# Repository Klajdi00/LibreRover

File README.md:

# LibreRover

LibreRover is a open-source, open-hardware educational robot designed for Arduino and robotics workshops.

## Hardware

The hardware parts mostly can be 3D printed. It is designed to fit affordable breakout boards. It is modular and expandable: If you want an encoder, use it. If not, no problem. More sensors? Just print the parts and stick it to the robot.
By using breakout boards for all sensors, the wiring is very flexible, at the cost of lots of wires thorugh the air. For a more permanent setup, consider hot glue and good cable management.

## Software

The Arduino framework is used. Feel free to choose an Arduino Nano (simple), an ESP32 (has WiFi) or another microcontroller. Several classes for an easy start are provided and can be used as needed:
- `Motor`: This makes a simple motor more accessible by taking care of the direction pins and PWM speed control. It is intended to be used with an L298N motor driver.
- `EncoderMotor`: A motor and an encoder together form an EncoderMotor. This class handles both, so the user can easily set the speed and make a wheel move a certain amount.

If you use the Arduino IDE, make sure to add the files in `software/lib/LibreRover` to your project. As an Alternative, consider using PlatformIO.

## Bill of Materials

| Component | Quantity | Estimated Cost | Notes |
|-----------|----------|----------------|-------|
| Arduino Nano | 1 | 3.40 € | Or compatible clone |
| DC Motors with Encoders | 2 | 2.80 € | TT motor; recommended to buy a set with wheels |
| Motor Driver (HW-201 or L298N) | 1 | 2.50 € | Dual H-bridge driver |
| 9V Battery | 1 | 3.50 € | Power supply |
| Jumper Wires | Several | 3.80 € | For connections |
| Light gate LM393 (for simple encoder) | 2 | 3.20 € | optional |
| HW-201 IR reflection sensor | 2 | 1.30 € | optional |
| VL53L0X ToF distance sensor | 3 | 4.00 € | optional |
| Others | - | 1.00 € | 9 V Battery cable, swith for turning on/off |

**Estimated Total Cost**: ~17 to 27 € (depending on your setup; excluding 3D printer)

## Hardware assembly

The mechanical parts are in `hardware/mechanical`. The full assembly is shown in `hardware/mechanical/Rover.f3z`.

1. Print the parts that you need:
	- Body
	- Mounting parts for your set of sensors
2. If you print 3D print the wheels (not recommended): Use rubber foam or similar so that they have some grip on the ground.
3. Assemble the motors
	- Screws work best.
	- As an alternative, use the clams `Clamp_Motor_Nose` and `Clamp_Motor_Body` together with `Pin_Motor`.
4. Assemble the glider by sticking it to the body frame. It will be the third contact point with the ground.
5. Assemble the sensors. The sensor mounts are fixed to the body frame with `Simple_pin` and friction. The distance sensors can be fixed to their mounts either by another pin (`Pin_VL53L0X`) or a clamp (`Clamp_VL53L0X`).
6. The 9V battery can be hold in place by `9V_Block_Mounting` on the bottom side of the frame.
7. Wire the electronics.

## Software setup

### Motor

When using the provided class for a simple motor, make sure to setup the correct pins and values.

The `Motor` needs:
- The pins connected to IN1 and IN 2 from the motor driver board (so set the direction).
- The pin connected to EN from the motor driver board. Make sure that PWM is supported on this pin.
- The minimum PWM value at which the motor starts moving. This is used to scale the speed.
- The maximum PWM value. This limits the effective voltage for the motor. Use it, when the motor is made for 6 V instead of the 9 V of the battery: `255 / (battery voltage) * (max. motor voltage)`.

The `EncoderMotor` takes
- The `Motor` to control
- The `SimpleEncoder` attatched to it
- The circumference of the wheel
- The amount of encoder pulses per revolution
- The maximum speed in mm/s.

```cpp
// Motor(forward_pin, backward_pin, pwm_pin, min_pwm, max_pwm)
Motor motor_left(9, 10, 11, 50, 255 / 9. * 6.5);

// EncoderMotor(motor, encoder, mm_per_revolution, pulses_per_revolution, max_speed)
EncoderMotor enc_motor_left(motor_left, encoder_left, 251, 40, 350);
```

## Software Usage

### Basic Movement Example

```cpp
#include <EncoderMotor.h>

// Initialize motors and encoders

void loop() {
    // Drive forward 250mm at 150mm/s
    motor_left.drive_distance(250, 150);
    motor_right.drive_distance(250, 150);
    
    // Wait for completion
    while(!motor_left.is_stopped() || !motor_right.is_stopped()) {
        // Update speed control and stop motor if target distance is reached
		motor_left.tick();
        motor_right.tick();
    }
}
```

## Credits

For creating the CAD files, I used these models:
- Arduino Nano: Arduino Nano by Nithish Cadex: https://grabcad.com/library/arduino-nano-36
- L298N board: Motor Driver L298n by Nithish Cadex: https://grabcad.com/library/motor-driver-l298n-2
- Light gate: IR motor speed encoder arduino WYC H2010 by Ahmed Asem: https://print.grabcad.com/library/ir-motor-speed-encoder-arduino-wyc-h2010-1
- HW-201 IR reflection sensor: HW-201 by Kevin McAleer: https://grabcad.com/library/hw-201-1
- VL53L0X ToF distance sensor: VL53L0X by Darhl Thomason: https://grabcad.com/library/vl53l0x-4

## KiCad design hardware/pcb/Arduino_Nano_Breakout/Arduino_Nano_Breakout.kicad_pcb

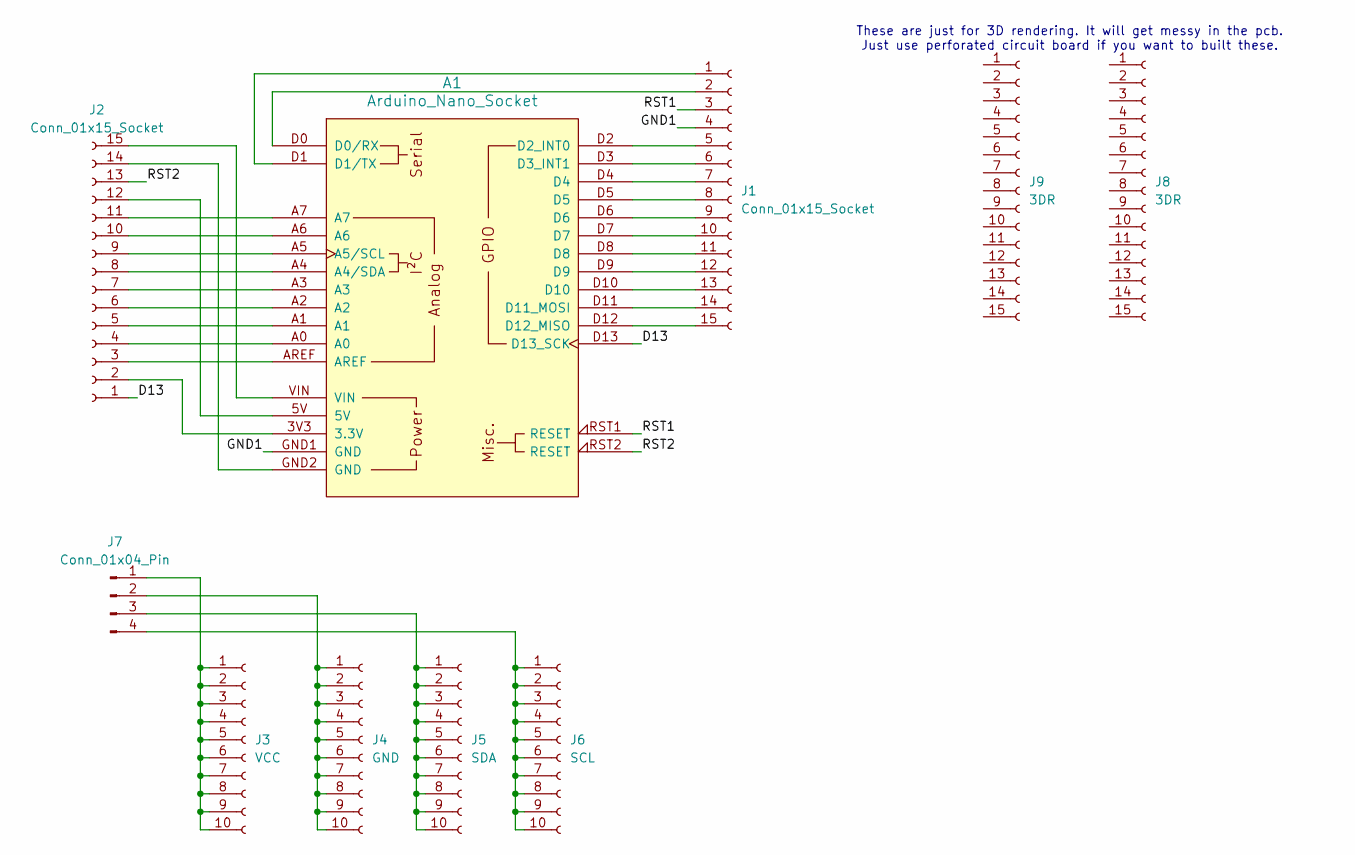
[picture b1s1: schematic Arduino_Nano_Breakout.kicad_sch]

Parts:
A1: Arduino_Nano_Socket
J1, J2: Conn_01x15_Socket; PinSocket_1x15_P2.54mm_Vertical
J3: VCC; PinSocket_1x10_P2.54mm_Vertical
J4: GND; PinSocket_1x10_P2.54mm_Vertical
J5: SDA; PinSocket_1x10_P2.54mm_Vertical
J6: SCL; PinSocket_1x10_P2.54mm_Vertical
J7: Conn_01x04_Pin; PinHeader_1x04_P2.54mm_Vertical
J8, J9: 3DR; PinSocket_1x15_P2.54mm_Vertical

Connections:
/D13: A1.D13 (D13_SCK), J2.1
/GND1: A1.GND1 (GND), J1.4
/RST1: A1.RST1 (RESET), J1.3
/RST2: A1.RST2 (RESET), J2.13
unnamed: A1.3V3 (3.3V), J2.2
unnamed: A1.A4 (A4/SDA), J2.8
unnamed: A1.A5 (A5/SCL), J2.9
unnamed: A1.D0 (D0/RX), J1.2
unnamed: A1.D1 (D1/TX), J1.1
unnamed: A1.D2 (D2_INT0), J1.5
unnamed: A1.D3 (D3_INT1), J1.6
unnamed: A1.D11 (D11_MOSI), J1.14
unnamed: A1.D12 (D12_MISO), J1.15
unnamed: A1.D4, J1.7
unnamed: A1.D5, J1.8
unnamed: A1.D6, J1.9
unnamed: A1.D7, J1.10
unnamed: A1.D8, J1.11
unnamed: A1.D9, J1.12
unnamed: A1.D10, J1.13
unnamed: A1.AREF, J2.3
unnamed: A1.A0, J2.4
unnamed: A1.A1, J2.5
unnamed: A1.A2, J2.6
unnamed: A1.A3, J2.7
unnamed: A1.A6, J2.10
unnamed: A1.A7, J2.11
unnamed: A1.5V, J2.12
unnamed: A1.GND2 (GND), J2.14
unnamed: A1.VIN, J2.15
unnamed: J3.1, J3.2, J3.3, J3.4, J3.5, J3.6, J3.7, J3.8, J3.9, J3.10, J7.1
unnamed: J4.1, J4.2, J4.3, J4.4, J4.5, J4.6, J4.7, J4.8, J4.9, J4.10, J7.2
unnamed: J5.1, J5.2, J5.3, J5.4, J5.5, J5.6, J5.7, J5.8, J5.9, J5.10, J7.3
unnamed: J6.1, J6.2, J6.3, J6.4, J6.5, J6.6, J6.7, J6.8, J6.9, J6.10, J7.4

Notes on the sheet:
These are just for 3D rendering. It will get messy in the pcb. Just use perforated circuit board if you want to built these.

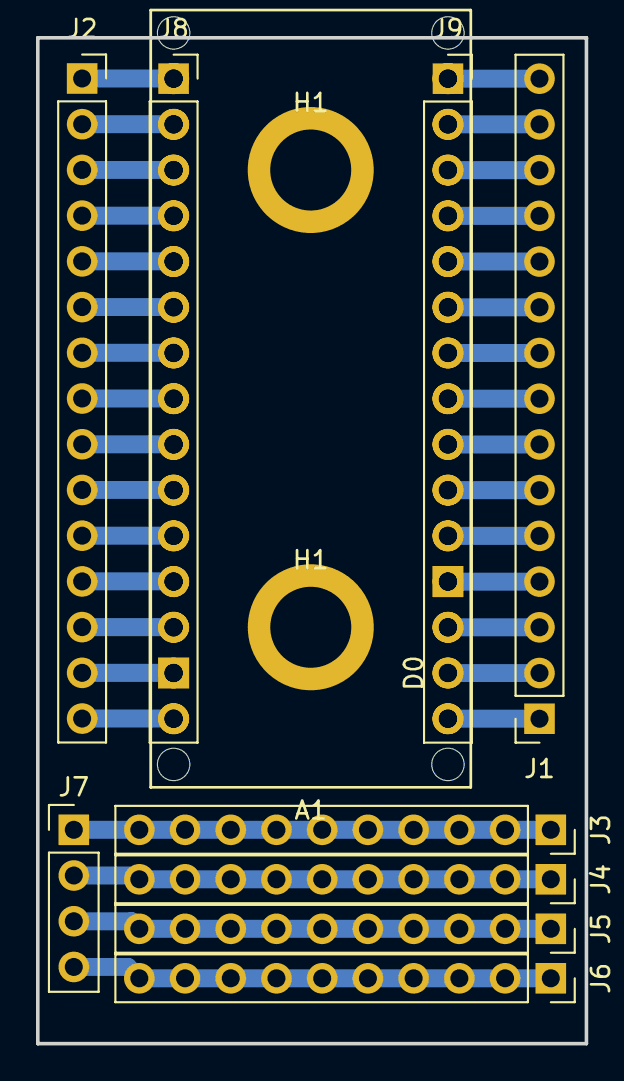
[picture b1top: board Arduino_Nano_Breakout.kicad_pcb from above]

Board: 2 copper layers, 30.5 x 55.9 mm, 12 parts (0 on the bottom side), 34 nets.

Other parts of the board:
H1, H1#2: M4; MountingHole_3.2mm_M3_DIN965_Pad

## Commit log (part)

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2026-02-21 Create LICENSE
2026-02-21 Create LICENSE-HARDWARE
2026-02-21 Small cleanup
2026-02-21 Added KiCad project for a simple Arduino Nano breakout board. Used for the 3D design; for building, just use a breadboard
2026-02-21 Added line follower example
2026-04-08 Fixed bug in mechanical base. Added Encoder Wheel with higher resolution.
2026-05-05 Added VL53L0X distance sensor. Added workshop tutorial.
